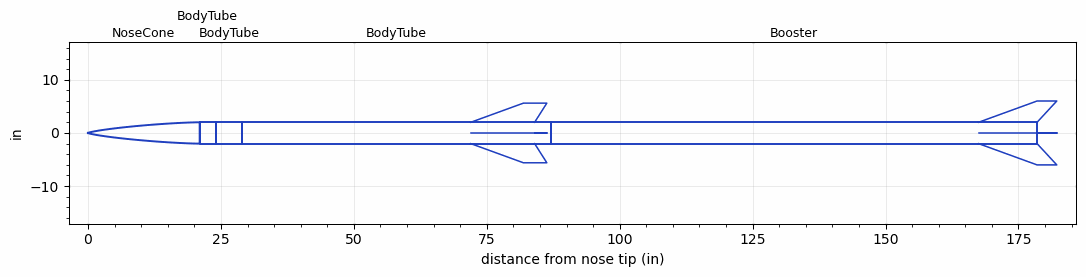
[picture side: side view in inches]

<RASAeroDocument>
 <FileVersion>2</FileVersion>
 <RocketDesign>
  <NoseCone>
   <Length>21</Length>
   <Diameter>4.02</Diameter>
   <Shape>Von Karman Ogive</Shape>
   <Location>0</Location>
  </NoseCone>
  <BodyTube>
   <Length>3</Length>
   <Diameter>4.02</Diameter>
   <Location>21</Location>
  </BodyTube>
  <BodyTube>
   <Length>5</Length>
   <Diameter>4.02</Diameter>
   <Location>24</Location>
  </BodyTube>
  <BodyTube>
   <Length>58</Length>
   <Diameter>4.02</Diameter>
   <Location>29</Location>
   <Fin>
    <Count>4</Count>
    <Chord>12</Chord>
    <Span>3.6</Span>
    <SweepDistance>9.891</SweepDistance>
    <TipChord>4.4</TipChord>
    <Thickness>0.25</Thickness>
    <LERadius>0.05</LERadius>
    <Location>15</Location>
    <AirfoilSection>Hexagonal</AirfoilSection>
    <FX1>1.2</FX1>
    <FX3>1.2</FX3>
   </Fin>
  </BodyTube>
  <Booster>
   <Length>91.5</Length>
   <Diameter>4.02</Diameter>
   <InsideDiameter>4.02</InsideDiameter>
   <Location>87</Location>
   <ShoulderLength>0</ShoulderLength>
   <Fin>
    <Count>4</Count>
    <Chord>11</Chord>
    <Span>4</Span>
    <SweepDistance>11</SweepDistance>
    <TipChord>3.7</TipChord>
    <Thickness>0.3</Thickness>
    <LERadius>0.05</LERadius>
    <Location>11</Location>
    <AirfoilSection>Hexagonal</AirfoilSection>
    <FX1>1.1</FX1>
    <FX3>1.1</FX3>
   </Fin>
  </Booster>
  <Surface>Polished</Surface>
  <ModifiedBarrowman>True</ModifiedBarrowman>
  <Turbulence>True</Turbulence>
  <UseBooster1>False</UseBooster1>
  <UseBooster2>False</UseBooster2>
 </RocketDesign>
 <LaunchSite>
  <Altitude>2000</Altitude>
  <Pressure>0</Pressure>
  <RodAngle>0</RodAngle>
  <RodLength>20</RodLength>
  <Temperature>70</Temperature>
  <WindSpeed>10</WindSpeed>
 </LaunchSite>
 <Recovery>
  <Altitude1>1000</Altitude1>
  <Altitude2>1000</Altitude2>
  <DeviceType1>None</DeviceType1>
  <DeviceType2>None</DeviceType2>
  <Event1>False</Event1>
  <Event2>False</Event2>
  <Size1>1</Size1>
  <Size2>1</Size2>
  <EventType1>None</EventType1>
  <EventType2>None</EventType2>
  <CD1>1.33</CD1>
  <CD2>1.33</CD2>
 </Recovery>
 <SimulationList>
  <Simulation>
   <SustainerEngine>M685W-PS  (AT)</SustainerEngine>
   <SustainerLaunchWt>34.9</SustainerLaunchWt>
   <SustainerNozzleDiameter>2.557</SustainerNozzleDiameter>
   <SustainerCG>55.92</SustainerCG>
   <SustainerIgnitionDelay>2</SustainerIgnitionDelay>
   <Booster1Engine>O5500X  (AT)</Booster1Engine>
   <Booster1LaunchWt>86.3</Booster1LaunchWt>
   <Booster1SeparationDelay>0</Booster1SeparationDelay>
   <Booster1IgnitionDelay>0</Booster1IgnitionDelay>
   <Booster1CG>107</Booster1CG>
   <Booster1NozzleDiameter>3.6</Booster1NozzleDiameter>
   <IncludeBooster1>True</IncludeBooster1>
   <Booster2Delay>0</Booster2Delay>
   <IncludeBooster2>False</IncludeBooster2>
   <TimetoApogee>75.28682</TimetoApogee>
   <MaxAltitude>92219.15</MaxAltitude>
   <MaxVelocity>2510.277</MaxVelocity>
  </Simulation>
 </SimulationList>
</RASAeroDocument>
